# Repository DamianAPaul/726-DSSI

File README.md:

# 726 Digital Sound Sequencing Instrument (726-DSSI)

A standalone digital synthesizer and 64-step sequencer designed around the Teensy 4.1.

The 726-DSSI is a personal embedded systems project combining real-time digital audio processing, custom C++ firmware, PCB design, physical controls, sequencing, and visual feedback.

## Features

- Up to 8 simultaneous oscillator, noise, or sample-based voices
- Per-voice filtering and amplitude envelopes
- 64-step sequencer
- Teensy 4.1 microcontroller
- PJRC Audio Shield
- SSD1306 OLED display
- MAX7219 8x8 LED matrix
- MCP23017 GPIO expansion
- CD74HC4067 analog multiplexing
- 3x4 keyboard matrix
- Custom C++ firmware using the Teensy Audio Library

## Hardware

I designed the schematic and PCB in KiCad, including custom schematic symbols and PCB footprints for several project-specific modules.

The first PCB revision has been fabricated, assembled, and validated; and is now awaiting shipping.

## Firmware

The firmware is written in C++ for the Teensy 4.1 using the Teensy Audio Library.

The firmware handles:

- Real-time audio synthesis and processing
- Voice management
- Sequencing
- Control scanning
- Analog multiplexing
- Keyboard input
- OLED and LED matrix feedback

## Repository Structure

- `726-DSSI_Firmware/` — Teensy C++ code, including the complete audio signal path
- `726-DSSI_CAD/` — KiCad schematic, PCB design files, custom footprint library, and gerbers
- `726-DSSI_Images/` — project images, mainly from prototyping phase

## Project Status

The breadboard prototype has been used for firmware and subsystem development. The first custom PCB revision has been fabricated, validated, and is awaiting shipping.

## Author

Damian Paul  
University of California, Berkeley  
Physics | Electrical Engineering & Computer Science

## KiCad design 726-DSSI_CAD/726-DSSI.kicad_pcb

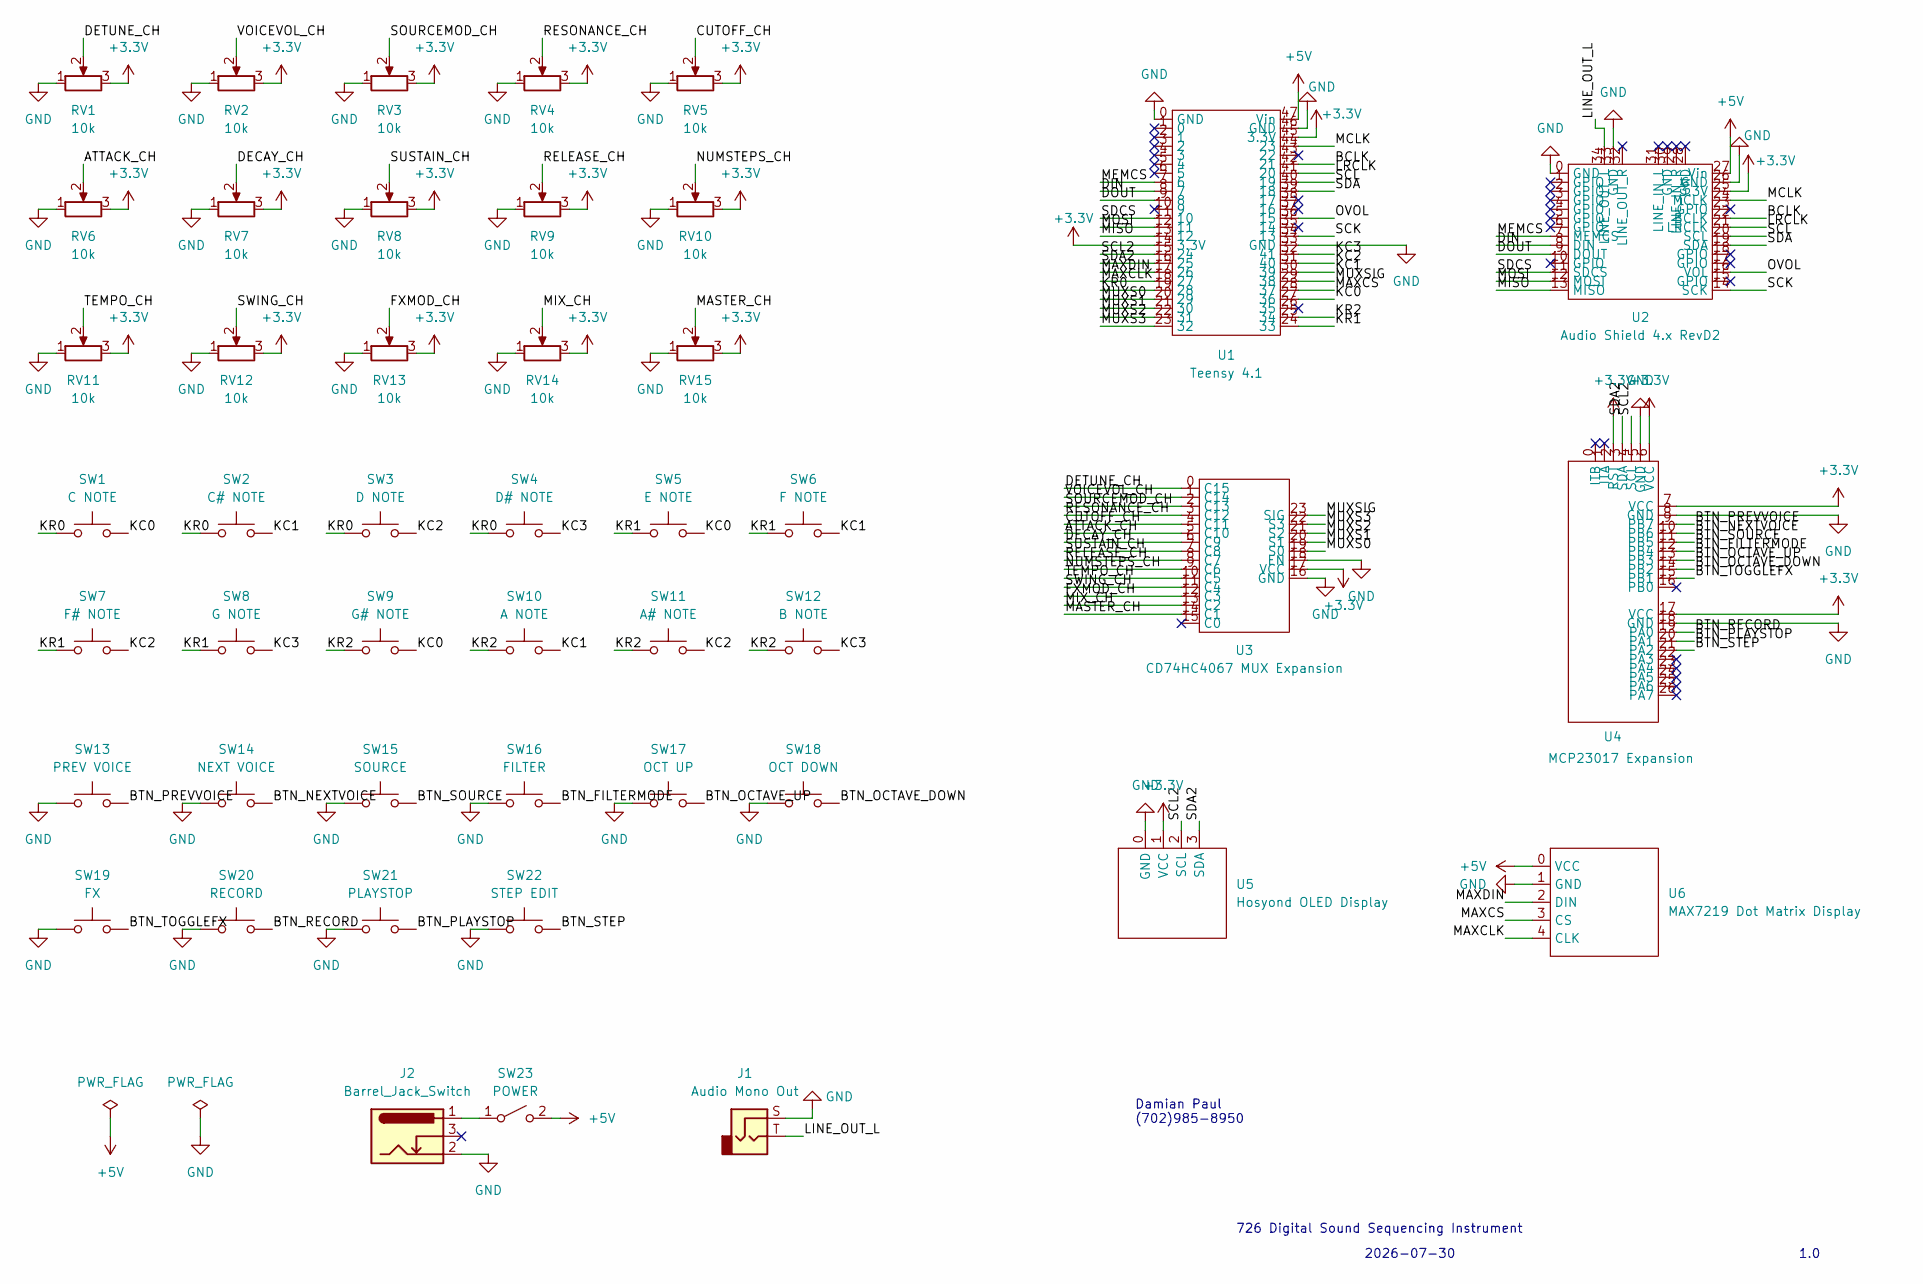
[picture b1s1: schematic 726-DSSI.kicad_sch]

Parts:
J1: Audio Mono Out; AudioJackOutMono
J2: Barrel_Jack_Switch; PJ102AH Power Jack
RV1, RV2, RV3, RV4, RV5, RV6, RV7, RV8, RV9, RV10, RV11, RV12, RV13, RV14, RV15: 10k; Potentiometer_Alps_RK09K_Single_Vertical
SW1: C NOTE; B3F-4050_ButtonSwitch
SW2: C# NOTE; B3F-4050_ButtonSwitch
SW3: D NOTE; B3F-4050_ButtonSwitch
SW4: D# NOTE; B3F-4050_ButtonSwitch
SW5: E NOTE; B3F-4050_ButtonSwitch
SW6: F NOTE; B3F-4050_ButtonSwitch
SW7: F# NOTE; B3F-4050_ButtonSwitch
SW8: G NOTE; B3F-4050_ButtonSwitch
SW9: G# NOTE; B3F-4050_ButtonSwitch
SW10: A NOTE; B3F-4050_ButtonSwitch
SW11: A# NOTE; B3F-4050_ButtonSwitch
SW12: B NOTE; B3F-4050_ButtonSwitch
SW13: PREV VOICE; B3F-4050_ButtonSwitch
SW14: NEXT VOICE; B3F-4050_ButtonSwitch
SW15: SOURCE; B3F-4050_ButtonSwitch
SW16: FILTER; B3F-4050_ButtonSwitch
SW17: OCT UP; B3F-4050_ButtonSwitch
SW18: OCT DOWN; B3F-4050_ButtonSwitch
SW19: FX; B3F-4050_ButtonSwitch
SW20: RECORD; B3F-4050_ButtonSwitch
SW21: PLAYSTOP; B3F-4050_ButtonSwitch
SW22: STEP EDIT; B3F-4050_ButtonSwitch
SW23: POWER; SW-T3-1A-A-A3-S1 ToggleSwitchPower
U1: Teensy 4.1
U2: Audio Shield 4.x RevD2; Teensy Audio Shield RevD
U3: CD74HC4067 MUX Expansion
U4: MCP23017 Expansion
U5: Hosyond OLED Display
U6: MAX7219 Dot Matrix Display

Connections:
+3.3V: RV1.3, RV2.3, RV3.3, RV4.3, RV5.3, RV6.3, RV7.3, RV8.3, RV9.3, RV10.3, RV11.3, RV12.3, RV13.3, RV14.3, RV15.3, U1.14 (3.3V), U1.45 (3.3V), U2.25 (3.3V), U3.17 (VCC), U4.2 (RST), U4.6 (VCC), U4.7 (VCC), U4.17 (VCC), U5.1 (VCC)
+5V: SW23.2 (B), U1.47 (Vin), U2.27 (Vin), U6.0 (VCC)
/ATTACK_CH: RV6.2, U3.5 (C10)
/BCLK: U1.42 (21), U2.22 (BCLK)
/BTN_FILTERMODE: SW16.2, U4.12 (PB4)
/BTN_NEXTVOICE: SW14.2, U4.10 (PB6)
/BTN_OCTAVE_DOWN: SW18.2, U4.14 (PB2)
/BTN_OCTAVE_UP: SW17.2, U4.13 (PB3)
/BTN_PLAYSTOP: SW21.2, U4.20 (PA1)
/BTN_PREVVOICE: SW13.2, U4.9 (PB7)
/BTN_RECORD: SW20.2, U4.19 (PA0)
/BTN_SOURCE: SW15.2, U4.11 (PB5)
/BTN_STEP: SW22.2, U4.21 (PA2)
/BTN_TOGGLEFX: SW19.2, U4.15 (PB1)
/CUTOFF_CH: RV5.2, U3.4 (C11)
/DECAY_CH: RV7.2, U3.6 (C9)
/DETUNE_CH: RV1.2, U3.0 (C15)
/DIN: U1.8 (7), U2.8 (DIN)
/DOUT: U1.9 (8), U2.9 (DOUT)
/FXMOD_CH: RV13.2, U3.12 (C3)
/KC0: SW1.2, SW5.2, SW9.2, U1.27 (36)
/KC1: SW2.2, SW6.2, SW10.2, U1.30 (39)
/KC2: SW3.2, SW7.2, SW11.2, U1.31 (40)
/KC3: SW4.2, SW8.2, SW12.2, U1.32 (41)
/KR0: SW1.1, SW2.1, SW3.1, SW4.1, U1.19 (28)
/KR1: SW5.1, SW6.1, SW7.1, SW8.1, U1.24 (33)
/KR2: SW9.1, SW10.1, SW11.1, SW12.1, U1.25 (34)
/LINE_OUT_L: J1.T, U2.34 (LINE_OUT_L)
/LRCLK: U1.41 (20), U2.21 (LRCLK)
/MASTER_CH: RV15.2, U3.14 (C1)
/MAXCLK: U1.18 (27), U6.4 (CLK)
/MAXCS: U1.28 (37), U6.3 (CS)
/MAXDIN: U1.17 (26), U6.2 (DIN)
/MCLK: U1.44 (23), U2.24 (MCLK)
/MEMCS: U1.7 (6), U2.7 (MEMCS)
/MISO: U1.13 (12), U2.13 (MISO)
/MIX_CH: RV14.2, U3.13 (C2)
/MOSI: U1.12 (11), U2.12 (MOSI)
/MUXS0: U1.20 (29), U3.19 (S0)
/MUXS1: U1.21 (30), U3.20 (S1)
/MUXS2: U1.22 (31), U3.21 (S2)
/MUXS3: U1.23 (32), U3.22 (S3)
/MUXSIG: U1.29 (38), U3.23 (SIG)
/NUMSTEPS_CH: RV10.2, U3.9 (C6)
/OVOL: U1.36 (15), U2.16 (VOL)
/RELEASE_CH: RV9.2, U3.8 (C7)
/RESONANCE_CH: RV4.2, U3.3 (C12)
/SCK: U1.34 (13), U2.14 (SCK)
/SCL: U1.40 (19), U2.20 (SCL)
/SCL2: U1.15 (24), U4.4 (SCL), U5.2 (SCL)
/SDA: U1.39 (18), U2.19 (SDA)
/SDA2: U1.16 (25), U4.3 (SDA), U5.3 (SDA)
/SDCS: U1.11 (10), U2.11 (SDCS)
/SOURCEMOD_CH: RV3.2, U3.2 (C13)
/SUSTAIN_CH: RV8.2, U3.7 (C8)
/SWING_CH: RV12.2, U3.11 (C4)
/TEMPO_CH: RV11.2, U3.10 (C5)
/VOICEVOL_CH: RV2.2, U3.1 (C14)
GND: J1.S, J2.2, RV1.1, RV2.1, RV3.1, RV4.1, RV5.1, RV6.1, RV7.1, RV8.1, RV9.1, RV10.1, RV11.1, RV12.1, RV13.1, RV14.1, RV15.1, SW13.1, SW14.1, SW15.1, SW16.1, SW17.1, SW18.1, SW19.1, SW20.1, SW21.1, SW22.1, U1.0 (GND), U1.33 (GND), U1.46 (GND), U2.0 (GND), U2.26 (GND), U2.33 (GND), U3.16 (GND), U3.18 (EN), U4.5 (GND), U4.8 (GND), U4.18 (GND), U5.0 (GND), U6.1 (GND)
unnamed: J2.1, SW23.1 (A)

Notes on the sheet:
726 Digital Sound Sequencing Instrument
1.0
Damian Paul (702)985-8950
2026-07-30

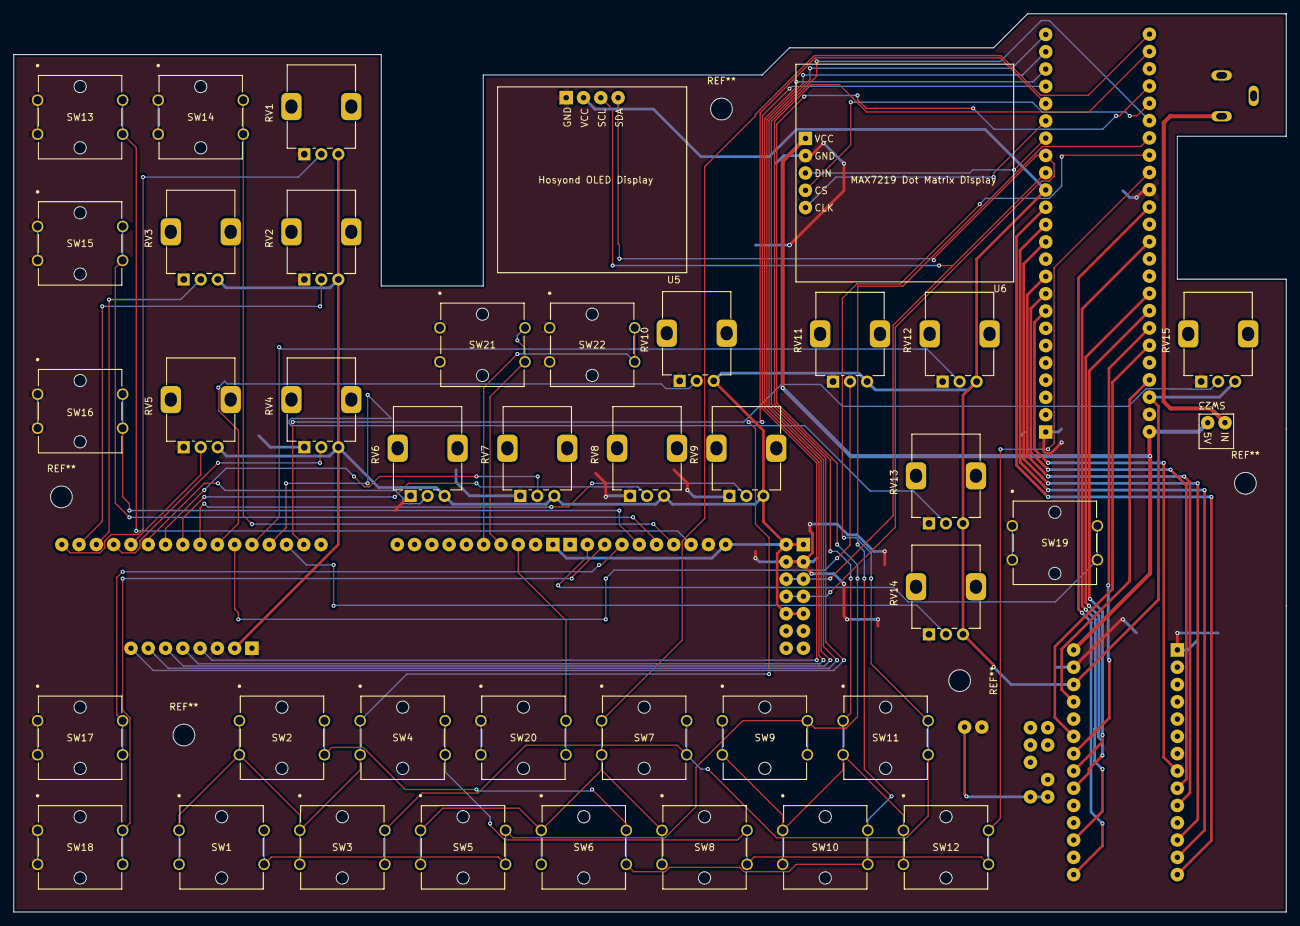
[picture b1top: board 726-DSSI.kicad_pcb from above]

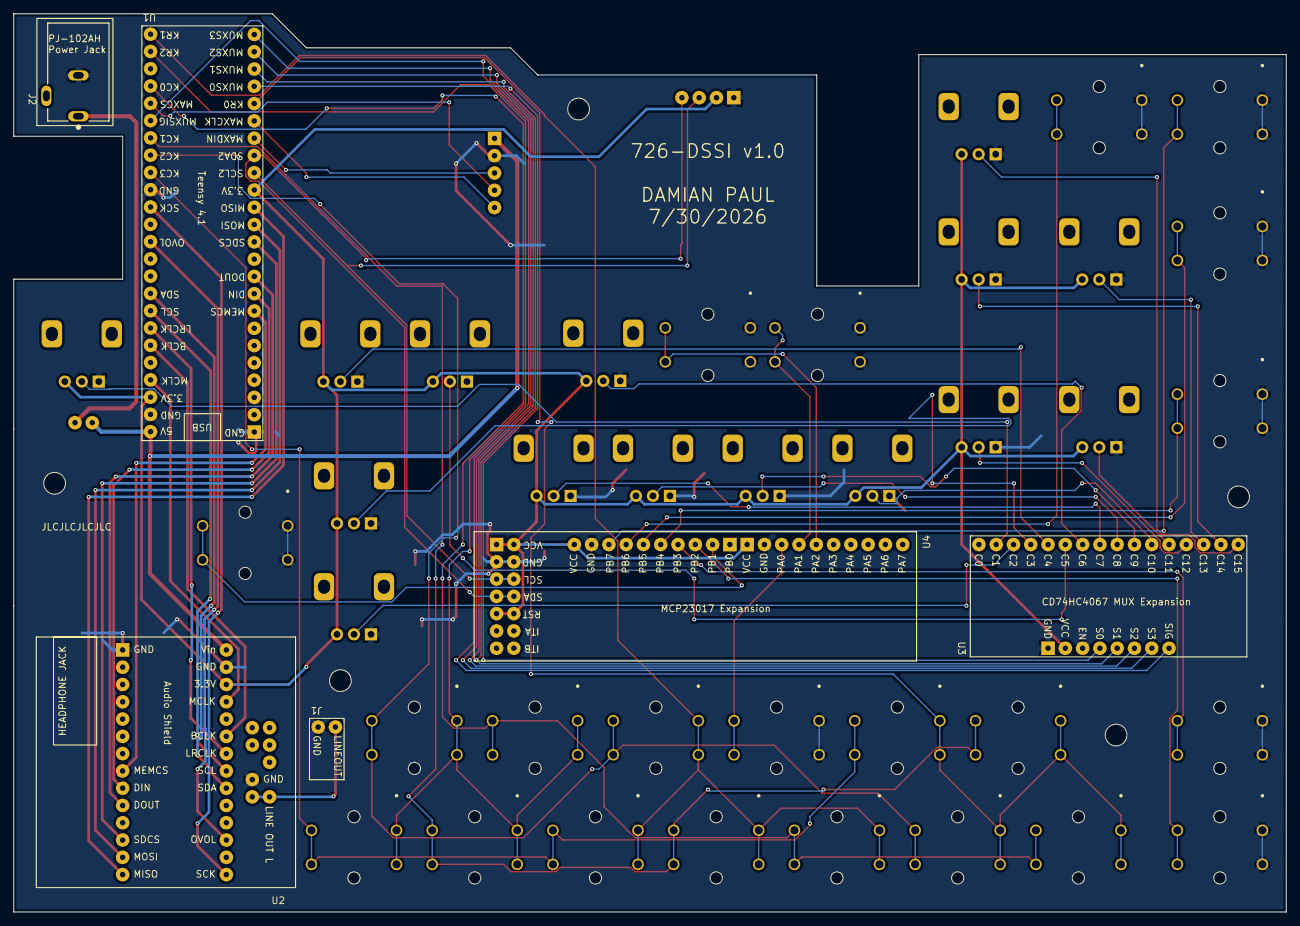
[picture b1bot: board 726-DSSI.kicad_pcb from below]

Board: 2 copper layers, 187.0 x 132.0 mm, 46 parts (6 on the bottom side), 60 nets.

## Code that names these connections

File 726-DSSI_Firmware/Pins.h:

#pragma once

#include <Arduino.h>

// ---------- I2C ----------
constexpr uint8_t I2C_SCL = 24;
constexpr uint8_t I2C_SDA = 25;

// ---------- Perform ----------
// Rows (outputs)
constexpr uint8_t KEY_ROW0 = 28;
constexpr uint8_t KEY_ROW1 = 33;
constexpr uint8_t KEY_ROW2 = 34;

// Columns (inputs)
constexpr uint8_t KEY_COL0 = 36;
constexpr uint8_t KEY_COL1 = 39;
constexpr uint8_t KEY_COL2 = 40;
constexpr uint8_t KEY_COL3 = 41;



// ---------- Multiplexer ----------

constexpr uint8_t MUX_S0 = 29;
constexpr uint8_t MUX_S1 = 30;
constexpr uint8_t MUX_S2 = 31;
constexpr uint8_t MUX_S3 = 32;

constexpr uint8_t MUX_SIG = A14;

// Multiplexer channels

constexpr uint8_t DETUNE_CH       = 15;
constexpr uint8_t VOICEVOL_CH     = 14;
constexpr uint8_t SOURCEMOD_CH    = 13;
constexpr uint8_t RESONANCE_CH    = 12;
constexpr uint8_t CUTOFF_CH       = 11;
constexpr uint8_t ATTACK_CH       = 10;
constexpr uint8_t DECAY_CH        = 9;
constexpr uint8_t SUSTAIN_CH      = 8;
constexpr uint8_t RELEASE_CH      = 7;
constexpr uint8_t NUMSTEPS_CH     = 6;
constexpr uint8_t TEMPO_CH        = 5;
constexpr uint8_t SWING_CH        = 4;
constexpr uint8_t FXMOD_CH        = 3;
constexpr uint8_t MIX_CH          = 2;
constexpr uint8_t MASTER_CH       = 1;

// ---------- MCP ----------

constexpr uint8_t MCP_ADDR = 0x20;

// Port A
constexpr uint8_t BTN_RECORD       = 0; // PA0
constexpr uint8_t BTN_PLAYSTOP     = 1; // PA1
constexpr uint8_t BTN_STEP         = 2; // PA2

// Port B
constexpr uint8_t BTN_TOGGLEFX    = 9;  // PB1
constexpr uint8_t BTN_OCTAVE_DOWN  = 10; // PB2;
constexpr uint8_t BTN_OCTAVE_UP    = 11; // PB3;
constexpr uint8_t BTN_FILTERMODE   = 12; // PB4
constexpr uint8_t BTN_SOURCE       = 13; // PB5
constexpr uint8_t BTN_NEXTVOICE    = 14; // PB6
constexpr uint8_t BTN_PREVVOICE    = 15; // PB7
